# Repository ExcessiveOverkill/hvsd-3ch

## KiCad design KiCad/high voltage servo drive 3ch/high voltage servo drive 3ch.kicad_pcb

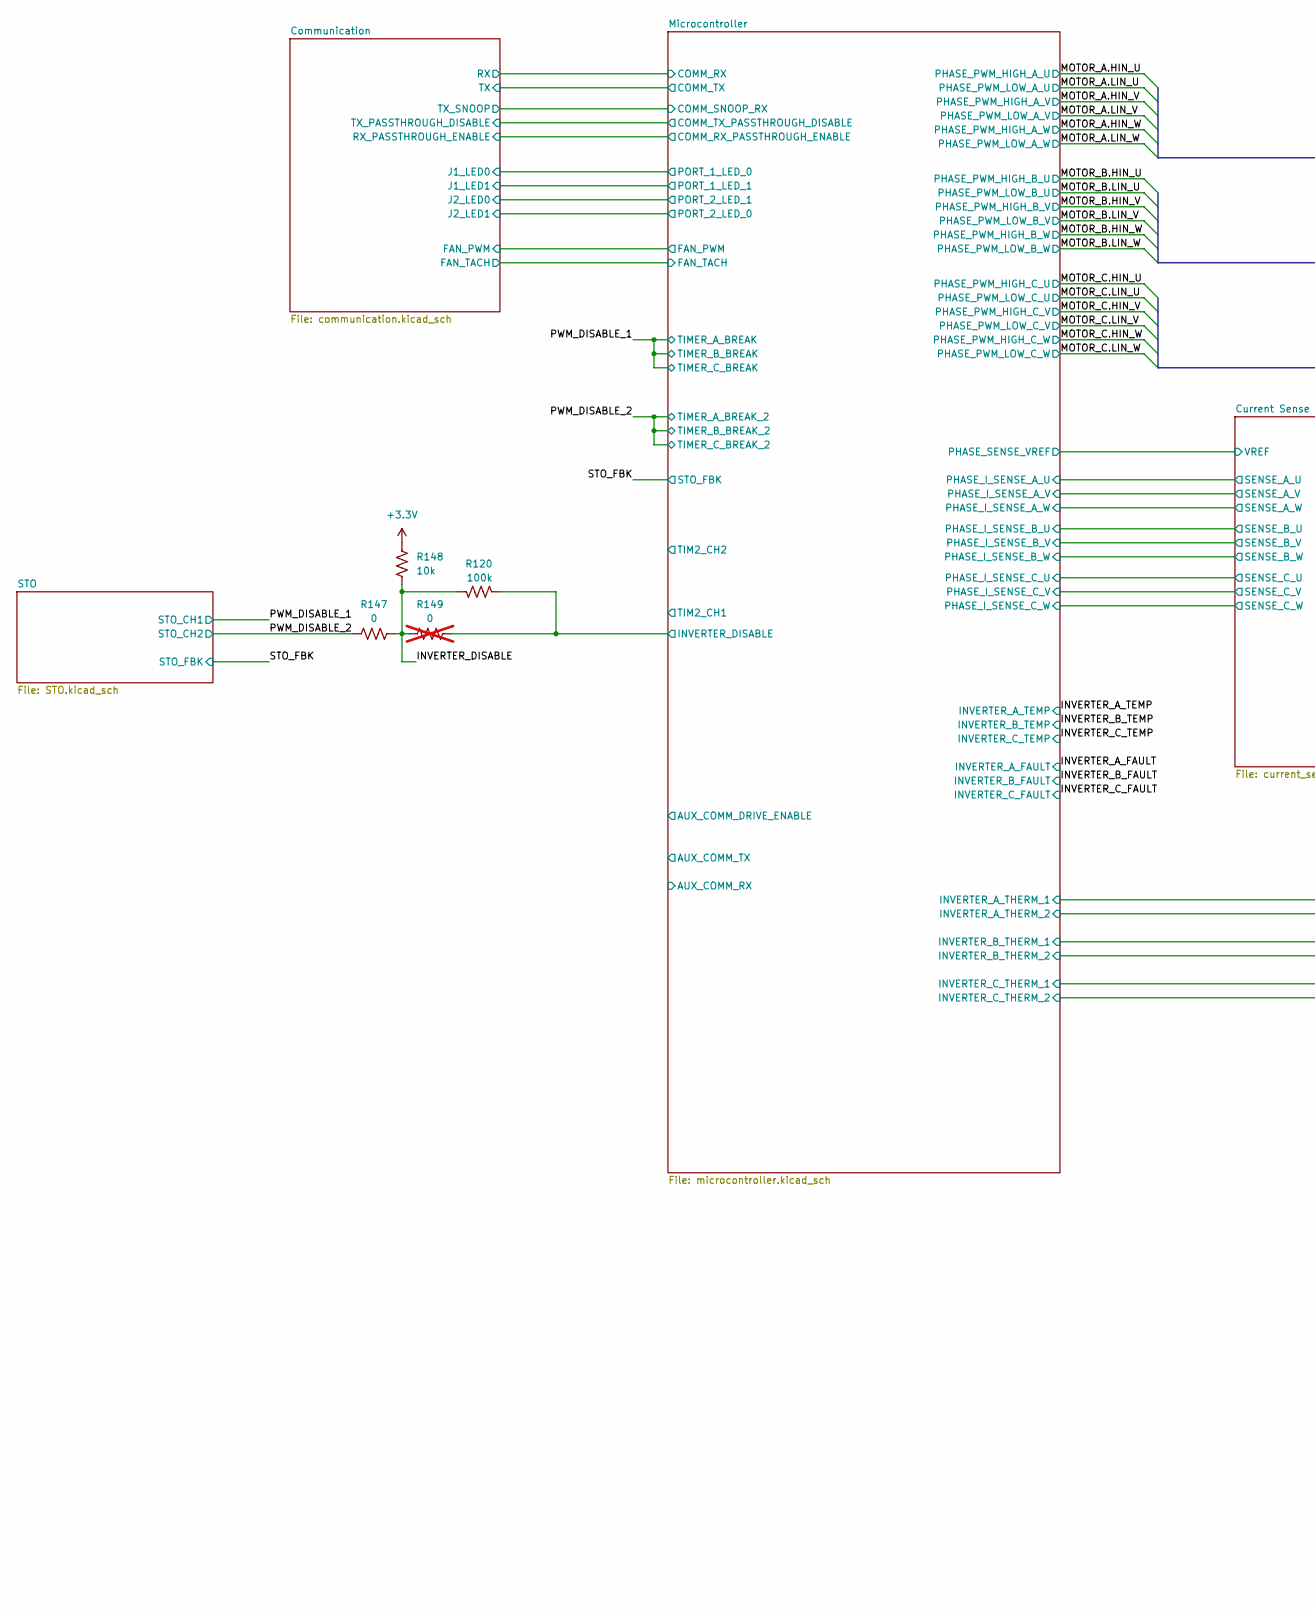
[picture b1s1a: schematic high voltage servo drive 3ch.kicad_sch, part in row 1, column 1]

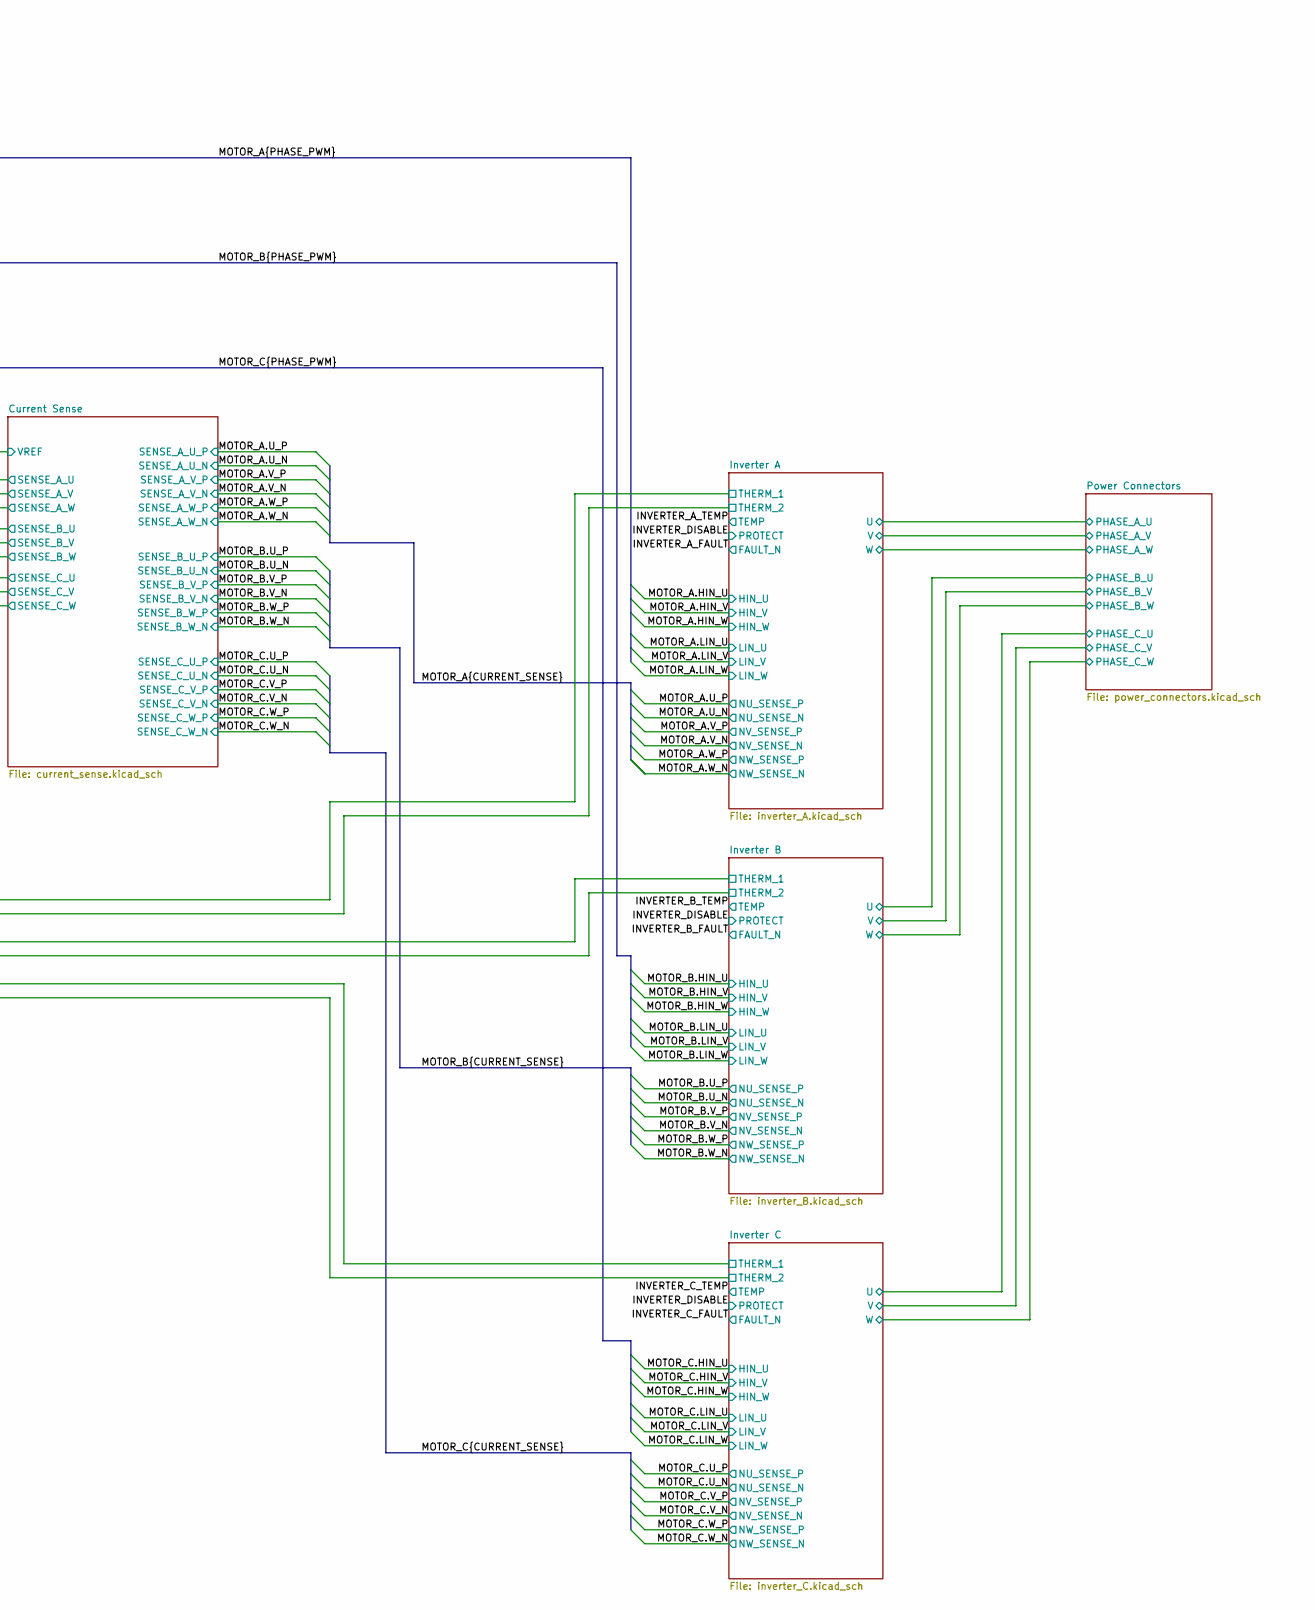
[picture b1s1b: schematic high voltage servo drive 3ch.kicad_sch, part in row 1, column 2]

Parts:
R120: 100k; R_0402_1005Metric; Part number RC0402FR-07100KL; LCSC# C60491
R147: 0; R_0402_1005Metric; Part number RC0402FR-070RL; LCSC# C106231
R148: 10k; R_0402_1005Metric; Part number RC0402FR-0710KL; LCSC# C60490
R149: 0; R_0402_1005Metric; Part number RC0402FR-070RL; LCSC# C106231; not fitted

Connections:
+3.3V: R148.2; also elsewhere on the board
/INVERTER_DISABLE: R120.2, R147.2, R148.1, R149.1; also elsewhere on the board
/Microcontroller/INVERTER_DISABLE: R120.1, R149.2; also elsewhere on the board
/PWM_DISABLE_2: R147.1; also elsewhere on the board

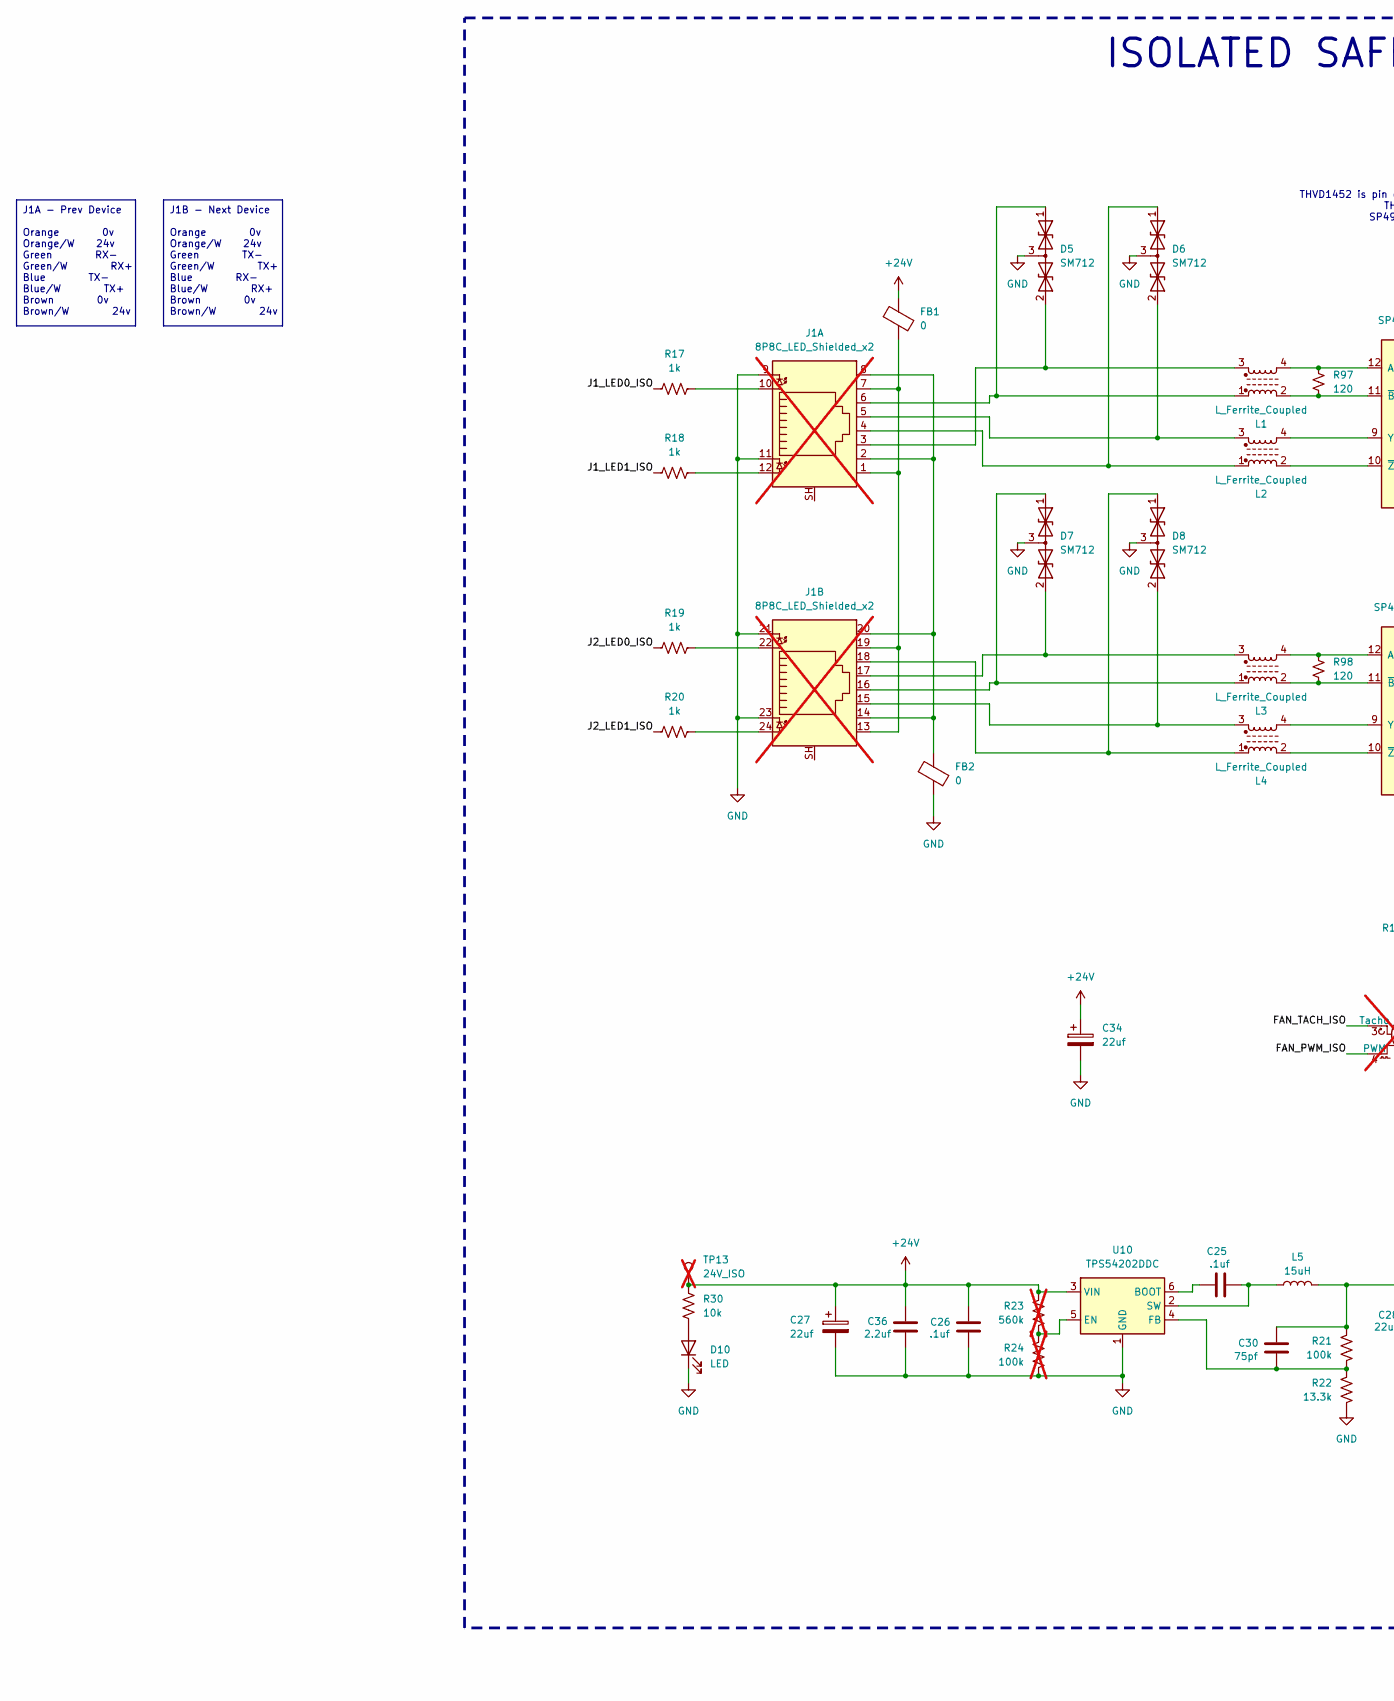
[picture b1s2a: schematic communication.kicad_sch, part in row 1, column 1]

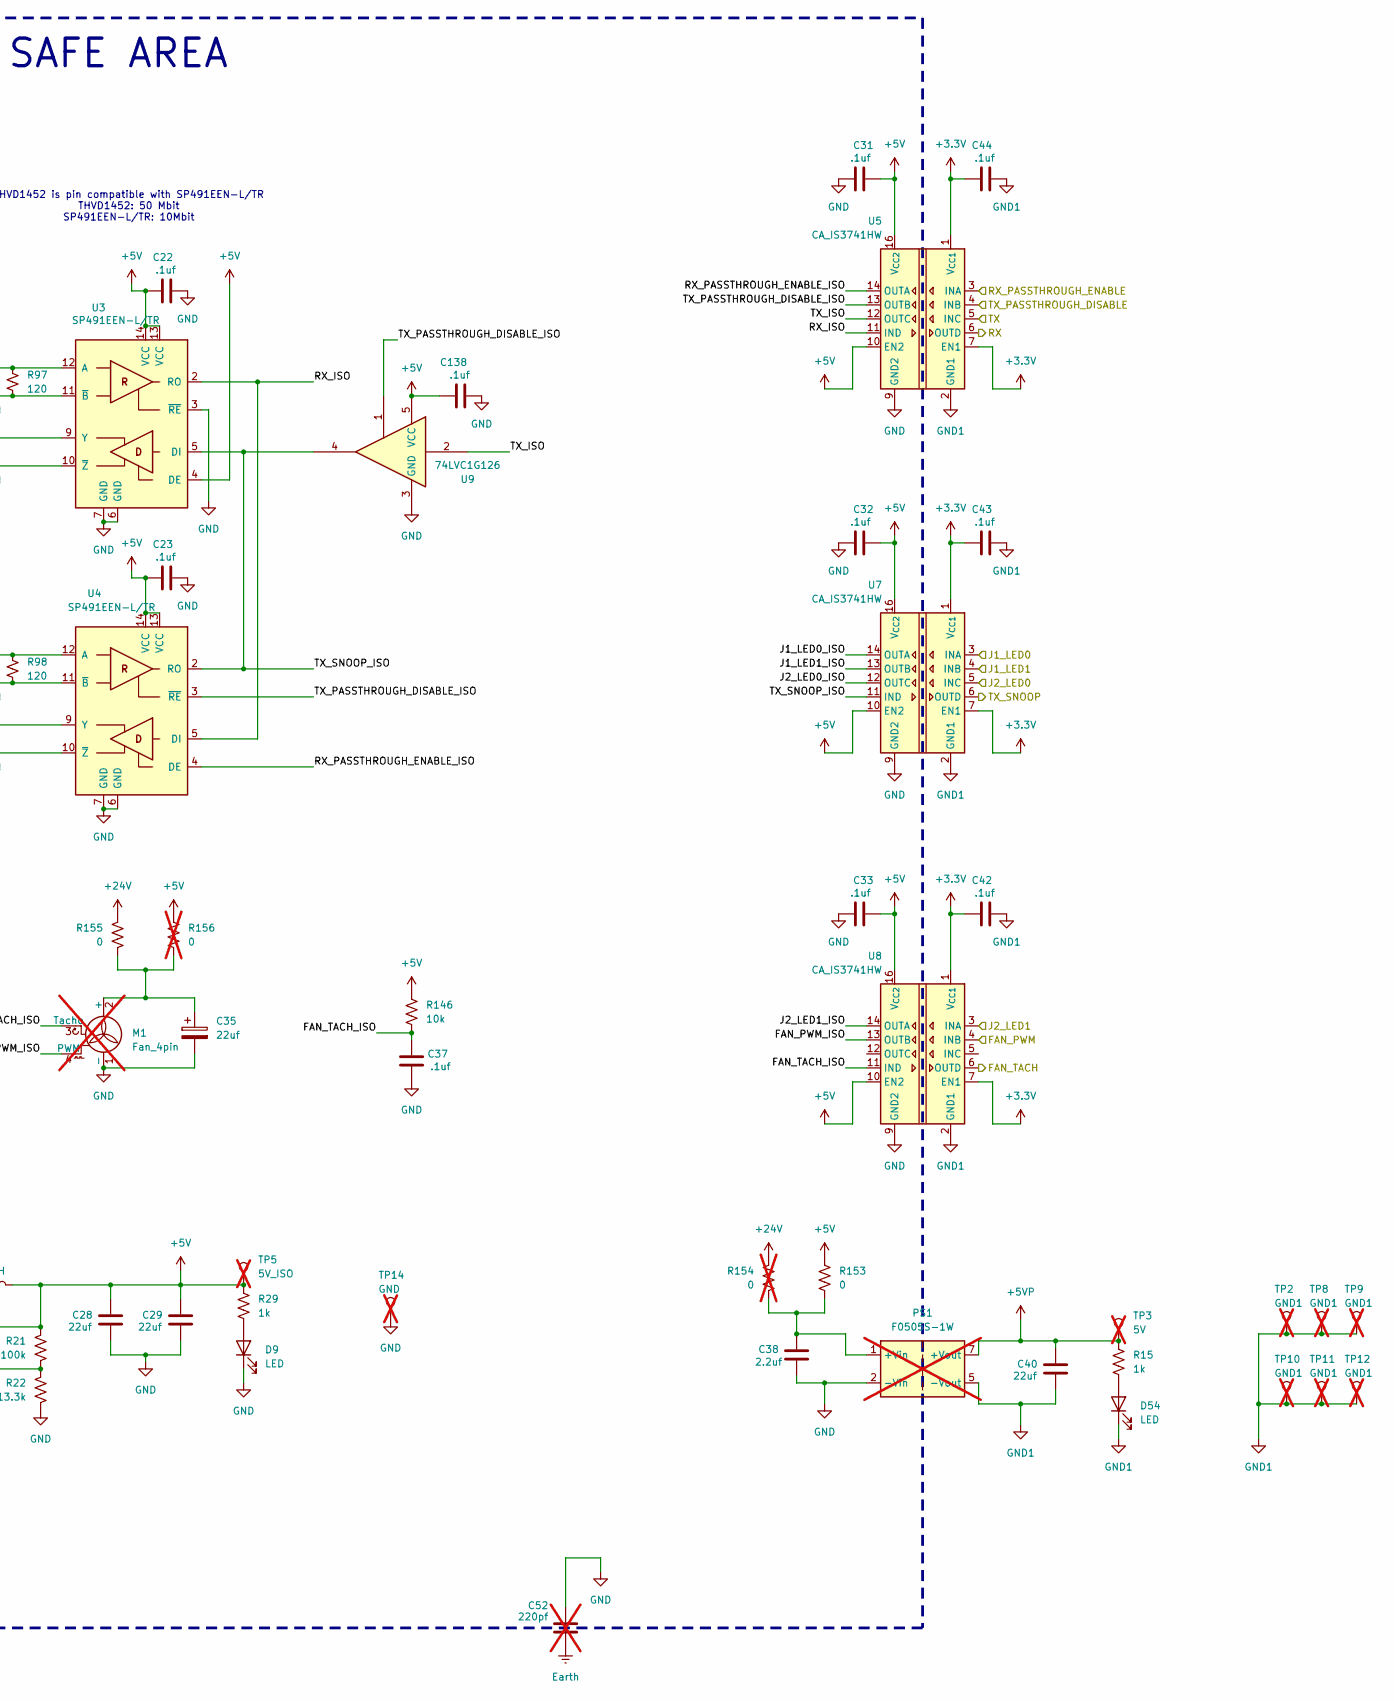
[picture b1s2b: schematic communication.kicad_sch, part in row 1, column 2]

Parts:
C22, C23, C25, C26, C31, C32, C33, C37, C42, C43, C44, C138: .1uf; C_0402_1005Metric; Part number CC0402KRX5R9BB104; LCSC# C105882
C27, C34, C35: 22uf; CP_Elec_6.3x5.9; Part number 189RV0014; LCSC# C7471876
C28, C29, C40: 22uf; C_1206_3216Metric; Part number CL31A226KAHNNNE; LCSC# C12891
C30: 75pf; C_0402_1005Metric; Part number CC0402JRNPO9BN750; LCSC# C107010
C36, C38: 2.2uf; C_1206_3216Metric; Part number CL31B225KBHNNNE; LCSC# C50254
C52: 220pf; C_Disc_D9.0mm_W5.0mm_P10.00mm; not fitted
D5, D6, D7, D8: SM712; SOT-23; Part number CDSOT23-SM712-ES; LCSC# C5199207
D9, D10, D54: LED; LED_0603_1608Metric; Part number XL-1608UGC-04; LCSC# C965804
FB1, FB2: 0; L_0805_2012Metric; Part number FRC0805P000 TS; LCSC# C2907288
J1: 8P8C_LED_Shielded_x2; RJ45_XDRJ-1609-002; Part number XDRJ-1609-002; LCSC# C7498193; not fitted
L1, L2, L3, L4: L_Ferrite_Coupled; SMD-4P,2x1.2mm; Part number CND-WCM0805M801-2; LCSC# C3020807
L5: 15uH; CY54_INDUCTOR; Part number CY54-15UH; LCSC# C2929432
M1: Fan_4pin; PinHeader_1x04_P2.54mm_Vertical; not fitted
PS1: F0505S-1W; Converter_DCDC_FXXS-1W; Part number F0505S-1WR3; LCSC# C2992398; not fitted
R15, R17, R18, R19, R20, R29: 1k; R_0402_1005Metric; Part number RC0402FR-071KL; LCSC# C106235
R21: 100k; R_0402_1005Metric; Part number RC0402FR-07100KL; LCSC# C60491
R22: 13.3k; R_0402_1005Metric; Part number RC0402FR-0713K3L; LCSC# C274352
R23: 560k; R_0402_1005Metric; Part number RC0402FR-07560KL; LCSC# C137958; not fitted
R24: 100k; R_0402_1005Metric; Part number RC0402FR-07100KL; LCSC# C60491; not fitted
R30, R146: 10k; R_0402_1005Metric; Part number RC0402FR-0710KL; LCSC# C60490
R97, R98: 120; R_0402_1005Metric; Part number RC0402FR-07120RL; LCSC# C114758
R153, R155: 0; R_0402_1005Metric; Part number RC0402FR-070RL; LCSC# C106231
R154, R156: 0; R_0402_1005Metric; Part number RC0402FR-070RL; LCSC# C106231; not fitted
TP2, TP8, TP9, TP10, TP11, TP12: GND1; TestPoint_THTPad_D2.0mm_Drill1.0mm; not fitted
TP3: 5V; TestPoint_Pad_D2.0mm; not fitted
TP5: 5V_ISO; TestPoint_Pad_D2.0mm; not fitted
TP13: 24V_ISO; TestPoint_Pad_D2.0mm; not fitted
TP14: GND; TestPoint_THTPad_D2.0mm_Drill1.0mm; not fitted
U3, U4: SP491EEN-L/TR; SOIC-14_3.9x8.7mm_P1.27mm; Part number SP491EEN-L/TR; LCSC# C32476
U5, U7, U8: CA_IS3741HW; SOIC-16W_7.5x10.3mm_P1.27mm; Part number CA-IS3741HW; LCSC# C428890
U9: 74LVC1G126; SOT-353_SC-70-5; Part number 74LVC1G126CT05ARCQ; LCSC# C48391411
U10: TPS54202DDC; SOT-23-6; Part number TPS54202DDCR; LCSC# C191884

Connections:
+3.3V: C42.1, C43.1, C44.1, U5.1 (V_{CC1}), U5.7 (EN1), U7.1 (V_{CC1}), U7.7 (EN1), U8.1 (V_{CC1}), U8.7 (EN1); also elsewhere on the board
+5V: C22.1, C23.1, C28.2, C29.2, C30.2, C31.1, C32.1, C33.1, C138.1, L5.2, R21.2, R29.2, R146.2, R153.2, R156.2, TP5.1, U3.4 (DE), U3.13 (VCC), U3.14 (VCC), U4.13 (VCC), U4.14 (VCC), U5.10 (EN2), U5.16 (V_{CC2}), U7.10 (EN2), U7.16 (V_{CC2}), U8.10 (EN2), U8.16 (V_{CC2}), U9.5 (VCC)
+5VP: C40.2, PS1.7 (+Vout), R15.2, TP3.1; also elsewhere on the board
+24V: C26.2, C27.1, C34.1, C36.2, FB1.1, R23.2, R30.2, R154.2, R155.2, TP13.1, U10.3 (VIN)
/Communication/FAN_PWM: U8.4 (INB); also elsewhere on the board
/Communication/FAN_PWM_ISO: M1.4 (PWM), U8.13 (OUTB)
/Communication/FAN_TACH: U8.6 (OUTD); also elsewhere on the board
/Communication/FAN_TACH_ISO: C37.1, M1.3 (Tacho), R146.1, U8.11 (IND)
/Communication/J1_LED0: U7.3 (INA); also elsewhere on the board
/Communication/J1_LED0_ISO: R17.1, U7.14 (OUTA)
/Communication/J1_LED1: U7.4 (INB); also elsewhere on the board
/Communication/J1_LED1_ISO: R18.1, U7.13 (OUTB)
/Communication/J2_LED0: U7.5 (INC); also elsewhere on the board
/Communication/J2_LED0_ISO: R19.1, U7.12 (OUTC)
/Communication/J2_LED1: U8.3 (INA); also elsewhere on the board
/Communication/J2_LED1_ISO: R20.1, U8.14 (OUTA)
/Communication/RX_ISO: U3.2 (RO), U4.5 (DI), U5.11 (IND)
/Communication/RX_PASSTHROUGH_ENABLE: U5.3 (INA); also elsewhere on the board
/Communication/RX_PASSTHROUGH_ENABLE_ISO: U4.4 (DE), U5.14 (OUTA)
/Communication/TX: U5.5 (INC); also elsewhere on the board
/Communication/TX_ISO: U5.12 (OUTC), U9.2
/Communication/TX_PASSTHROUGH_DISABLE: U5.4 (INB); also elsewhere on the board
/Communication/TX_PASSTHROUGH_DISABLE_ISO: U4.3 (~RE), U5.13 (OUTB), U9.1
/Communication/TX_SNOOP: U7.6 (OUTD); also elsewhere on the board
/Communication/TX_SNOOP_ISO: U3.5 (DI), U4.2 (RO), U7.11 (IND), U9.4
/Microcontroller/COMM_RX: U5.6 (OUTD); also elsewhere on the board
GND: C22.2, C23.2, C26.1, C27.2, C28.1, C29.1, C31.2, C32.2, C33.2, C34.2, C35.2, C36.1, C37.2, C38.1, C52.2, C138.2, D5.3 (common), D6.3 (common), D7.3 (common), D8.3 (common), D9.1 (K), D10.1 (K), FB2.2, J1.9, J1.11, J1.21, J1.23, M1.1 (-), PS1.2 (-Vin), R22.1, R24.1, TP14.1, U3.3 (~RE), U3.6 (GND), U3.7 (GND), U4.6 (GND), U4.7 (GND), U5.9 (GND2), U5.15 (GND2), U7.9 (GND2), U7.15 (GND2), U8.9 (GND2), U8.15 (GND2), U9.3 (GND), U10.1 (GND)
unnamed: D5.1 (A1), J1.6, L1.1
unnamed: D5.2 (A2), J1.3, L1.3
unnamed: D6.1 (A1), J1.4, L2.1
unnamed: D6.2 (A2), J1.5, L2.3
unnamed: D7.1 (A1), J1.16, L3.1
unnamed: D7.2 (A2), J1.17, L3.3
unnamed: D8.1 (A1), J1.18, L4.1
unnamed: D8.2 (A2), J1.15, L4.3
unnamed: D9.2 (A), R29.1
unnamed: D10.2 (A), R30.1
unnamed: D54.2 (A), R15.1
unnamed: FB1.2, J1.1, J1.7, J1.13, J1.19
unnamed: FB2.1, J1.2, J1.8, J1.14, J1.20
unnamed: J1.10, R17.2
unnamed: J1.12, R18.2
unnamed: J1.22, R19.2
unnamed: J1.24, R20.2
unnamed: C35.1, M1.2 (+), R155.1, R156.1
unnamed: C38.2, PS1.1 (+Vin), R153.1, R154.1
unnamed: L1.4, R97.1, U3.12 (A)
unnamed: L2.4, U3.9 (Y)
unnamed: L1.2, R97.2, U3.11 (~B)
unnamed: L2.2, U3.10 (~Z)
unnamed: L3.4, R98.1, U4.12 (A)
unnamed: L4.4, U4.9 (Y)
unnamed: L3.2, R98.2, U4.11 (~B)
unnamed: L4.2, U4.10 (~Z)
unnamed: C25.1, U10.6 (BOOT)
unnamed: R23.1, R24.2, U10.5 (EN)
unnamed: C30.1, R21.1, R22.2, U10.4 (FB)
unnamed: C25.2, L5.1, U10.2 (SW)

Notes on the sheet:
J1B - Next Device Orange 0v Orange/W 24v Green TX- Green/W TX+ Blue RX- Blue/W RX+ Brown 0v Brown/W 24v
J1A - Prev Device Orange 0v Orange/W 24v Green RX- Green/W RX+ Blue TX- Blue/W TX+ Brown 0v Brown/W 24v
THVD1452 is pin compatible with SP491EEN-L/TR THVD1452: 50 Mbit SP491EEN-L/TR: 10Mbit
ISOLATED SAFE AREA

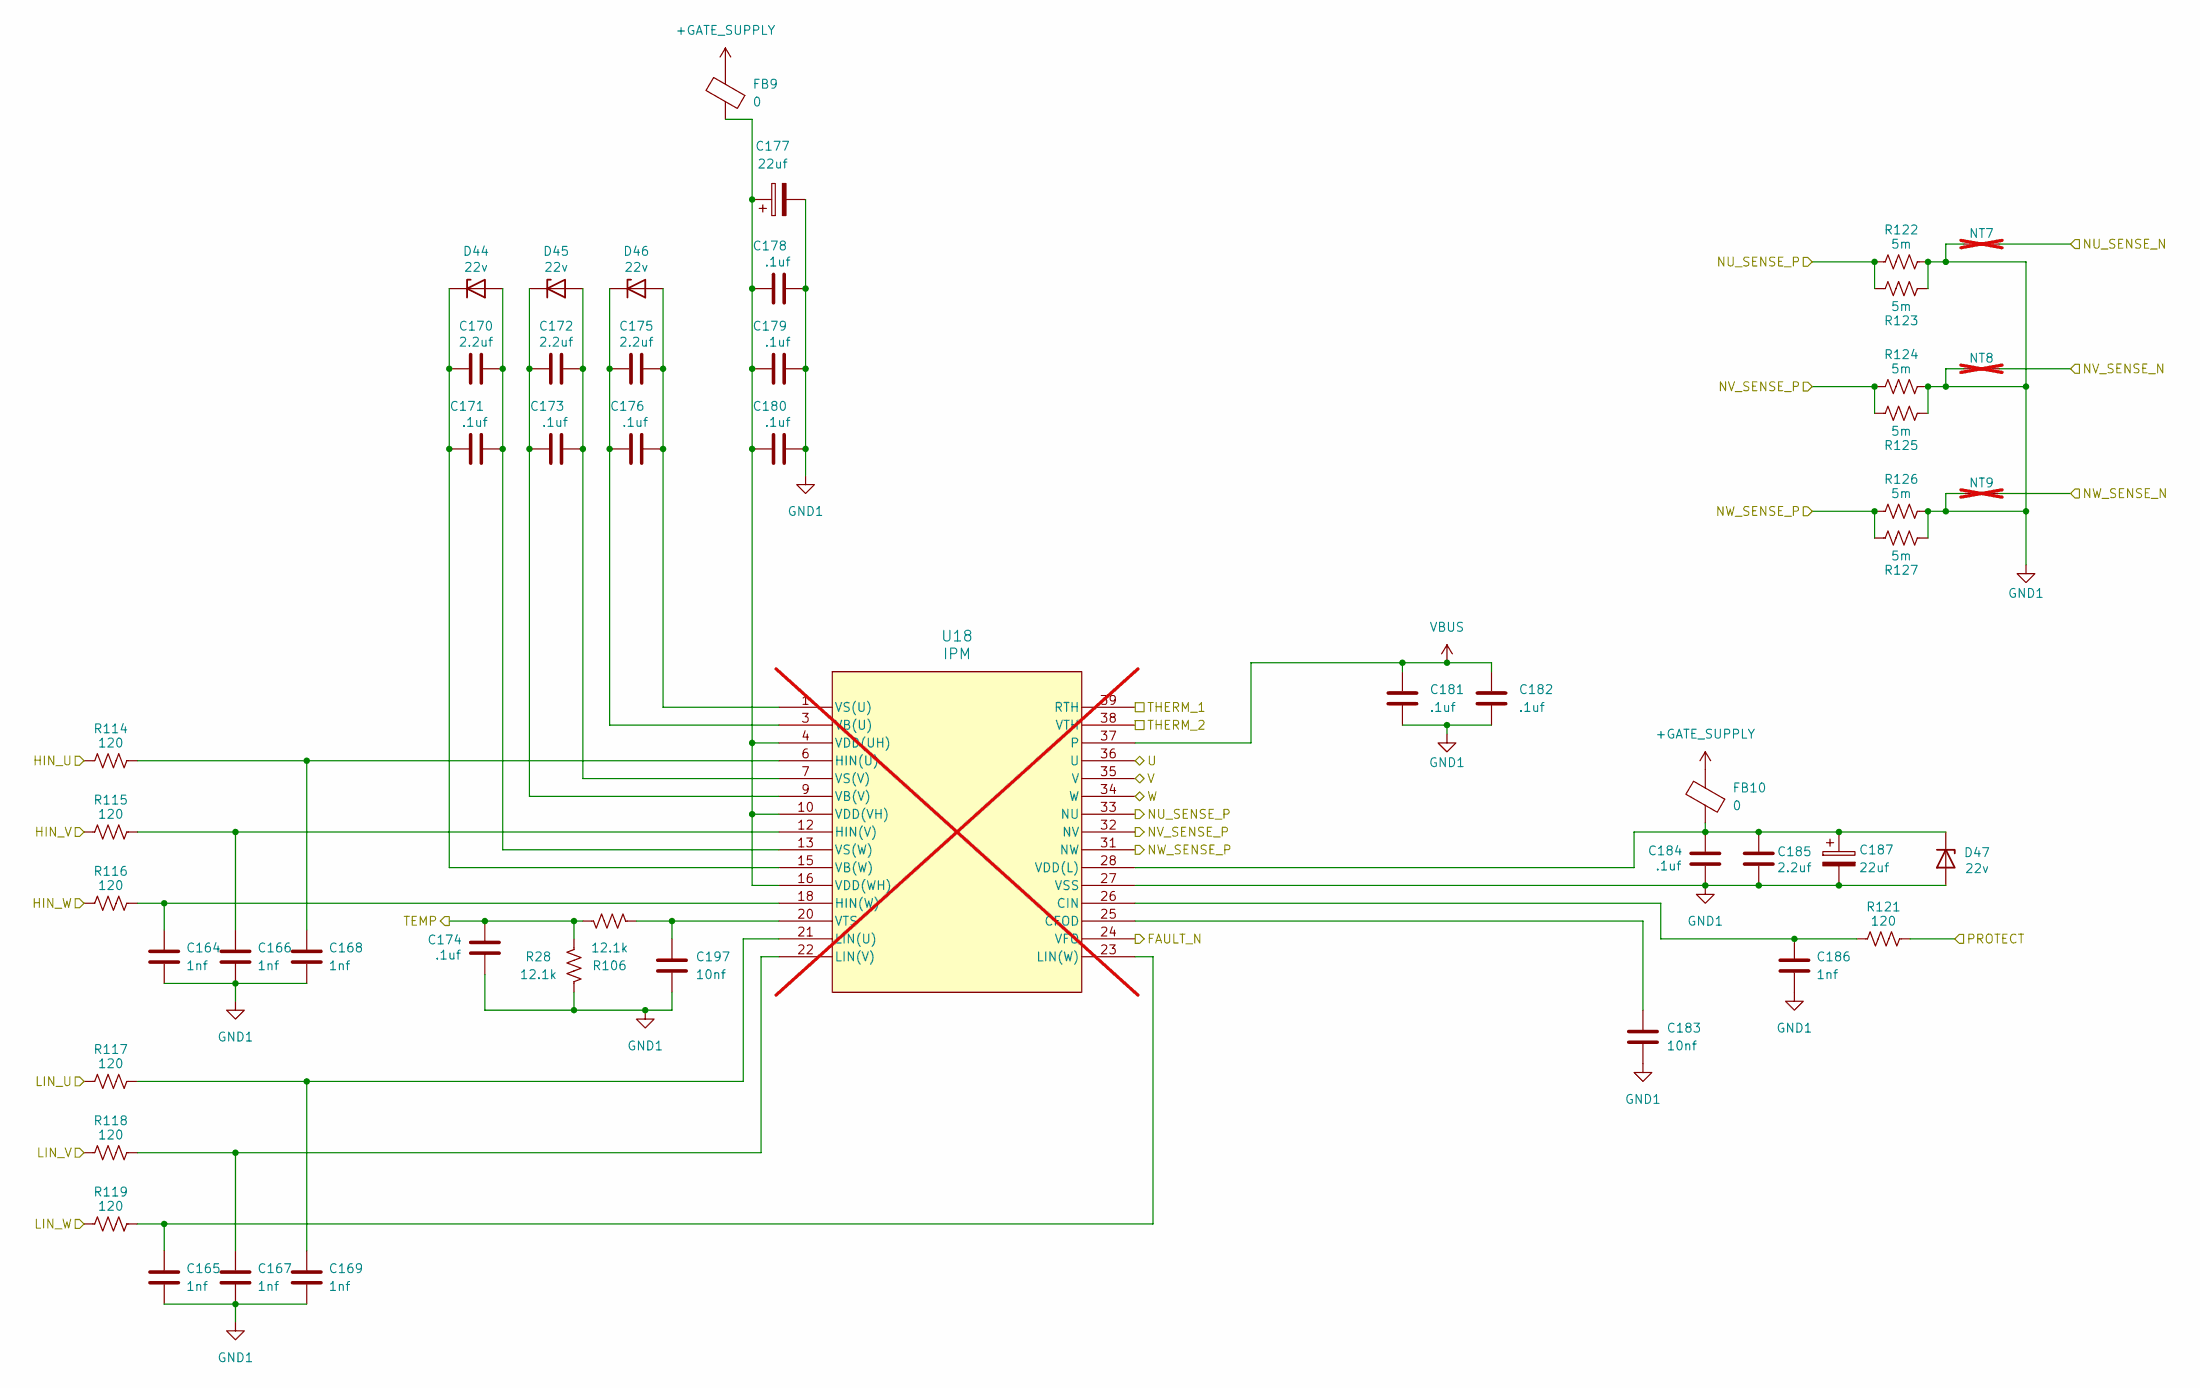
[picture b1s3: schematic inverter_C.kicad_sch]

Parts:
C164, C165, C166, C167, C168, C169, C186: 1nf; C_0402_1005Metric; Part number CC0402KRX7R9BB102; LCSC# C106205
C170, C172, C175, C185: 2.2uf; C_1206_3216Metric; Part number CL31B225KBHNNNE; LCSC# C50254
C171, C173, C174, C176, C178, C179, C180, C184: .1uf; C_0402_1005Metric; Part number CC0402KRX5R9BB104; LCSC# C105882
C177, C187: 22uf; CP_Elec_6.3x5.9; Part number 189RV0014; LCSC# C7471876
C181, C182: .1uf; C_1812_4532Metric; Part number NV1812B104K102CEMN; LCSC# C780707
C183, C197: 10nf; C_0402_1005Metric; Part number CC0402KRX7R9BB103; LCSC# C60133
D44, D45, D46, D47: 22v; D_SMA; Part number SMA2Z22A; LCSC# C7440711
FB9, FB10: 0; L_0805_2012Metric; Part number FRC0805P000 TS; LCSC# C2907288
NT7, NT8, NT9: NetTie_2; NetTie-2_SMD_Pad0.2mm; not fitted
R28, R106: 12.1k; R_0402_1005Metric; Part number RC0402FR-0712K1L; LCSC# C132157
R114, R115, R116, R117, R118, R119, R121: 120; R_0402_1005Metric; Part number RC0402FR-07120RL; LCSC# C114758
R122, R123, R124, R125, R126, R127: 5m; R_1206_3216Metric; Part number FRM121WFR005TM; LCSC# C7419996
U18: IPM; DIP39_54.5X31.0_MODGC_OSI; not fitted

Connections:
+GATE_SUPPLY: FB9.2, FB10.2; also elsewhere on the board
/INVERTER_C_FAULT: U18.24 (VFO); also elsewhere on the board
/INVERTER_C_TEMP: C174.2, R28.1, R106.1; also elsewhere on the board
/INVERTER_DISABLE: R121.2; also elsewhere on the board
/Inverter C/THERM_1: U18.39 (RTH); also elsewhere on the board
/Inverter C/U: U18.36 (U); also elsewhere on the board
/Inverter C/V: U18.35 (V); also elsewhere on the board
/Inverter C/W: U18.34 (W); also elsewhere on the board
/MOTOR_C.HIN_U: R114.1; also elsewhere on the board
/MOTOR_C.HIN_V: R115.1; also elsewhere on the board
/MOTOR_C.HIN_W: R116.1; also elsewhere on the board
/MOTOR_C.LIN_U: R117.1; also elsewhere on the board
/MOTOR_C.LIN_V: R118.1; also elsewhere on the board
/MOTOR_C.LIN_W: R119.1; also elsewhere on the board
/MOTOR_C.U_N: NT7.2; also elsewhere on the board
/MOTOR_C.U_P: R122.1, R123.2, U18.33 (NU); also elsewhere on the board
/MOTOR_C.V_N: NT8.2; also elsewhere on the board
/MOTOR_C.V_P: R124.1, R125.2, U18.32 (NV); also elsewhere on the board
/MOTOR_C.W_N: NT9.2; also elsewhere on the board
/MOTOR_C.W_P: R126.1, R127.2, U18.31 (NW); also elsewhere on the board
/Microcontroller/INVERTER_C_THERM: U18.38 (VTH); also elsewhere on the board
unnamed: C170.2, C171.2, D44.2 (A), U18.13 (VS(W))
unnamed: C170.1, C171.1, D44.1 (K), U18.15 (VB(W))
unnamed: C172.2, C173.2, D45.2 (A), U18.7 (VS(V))
unnamed: C172.1, C173.1, D45.1 (K), U18.9 (VB(V))
unnamed: C175.2, C176.2, D46.2 (A), U18.1 (VS(U))
unnamed: C175.1, C176.1, D46.1 (K), U18.3 (VB(U))
unnamed: C184.2, C185.1, C187.1, D47.1 (K), FB10.1, U18.28 (VDD(L))
unnamed: C183.1, U18.25 (CFOD)
unnamed: C186.1, R121.1, U18.26 (CIN)
unnamed: C168.1, R114.2, U18.6 (HIN(U))
unnamed: C166.1, R115.2, U18.12 (HIN(V))
unnamed: C164.1, R116.2, U18.18 (HIN(W))
unnamed: C169.1, R117.2, U18.21 (LIN(U))
unnamed: C167.1, R118.2, U18.22 (LIN(V))
unnamed: C165.1, R119.2, U18.23 (LIN(W))
unnamed: C177.1, C178.1, C179.1, C180.1, FB9.1, U18.4 (VDD(UH)), U18.10 (VDD(VH)), U18.16 (VDD(WH))
unnamed: C197.1, R106.2, U18.20 (VTS)
VBUS: C181.1, C182.1, U18.37; also elsewhere on the board

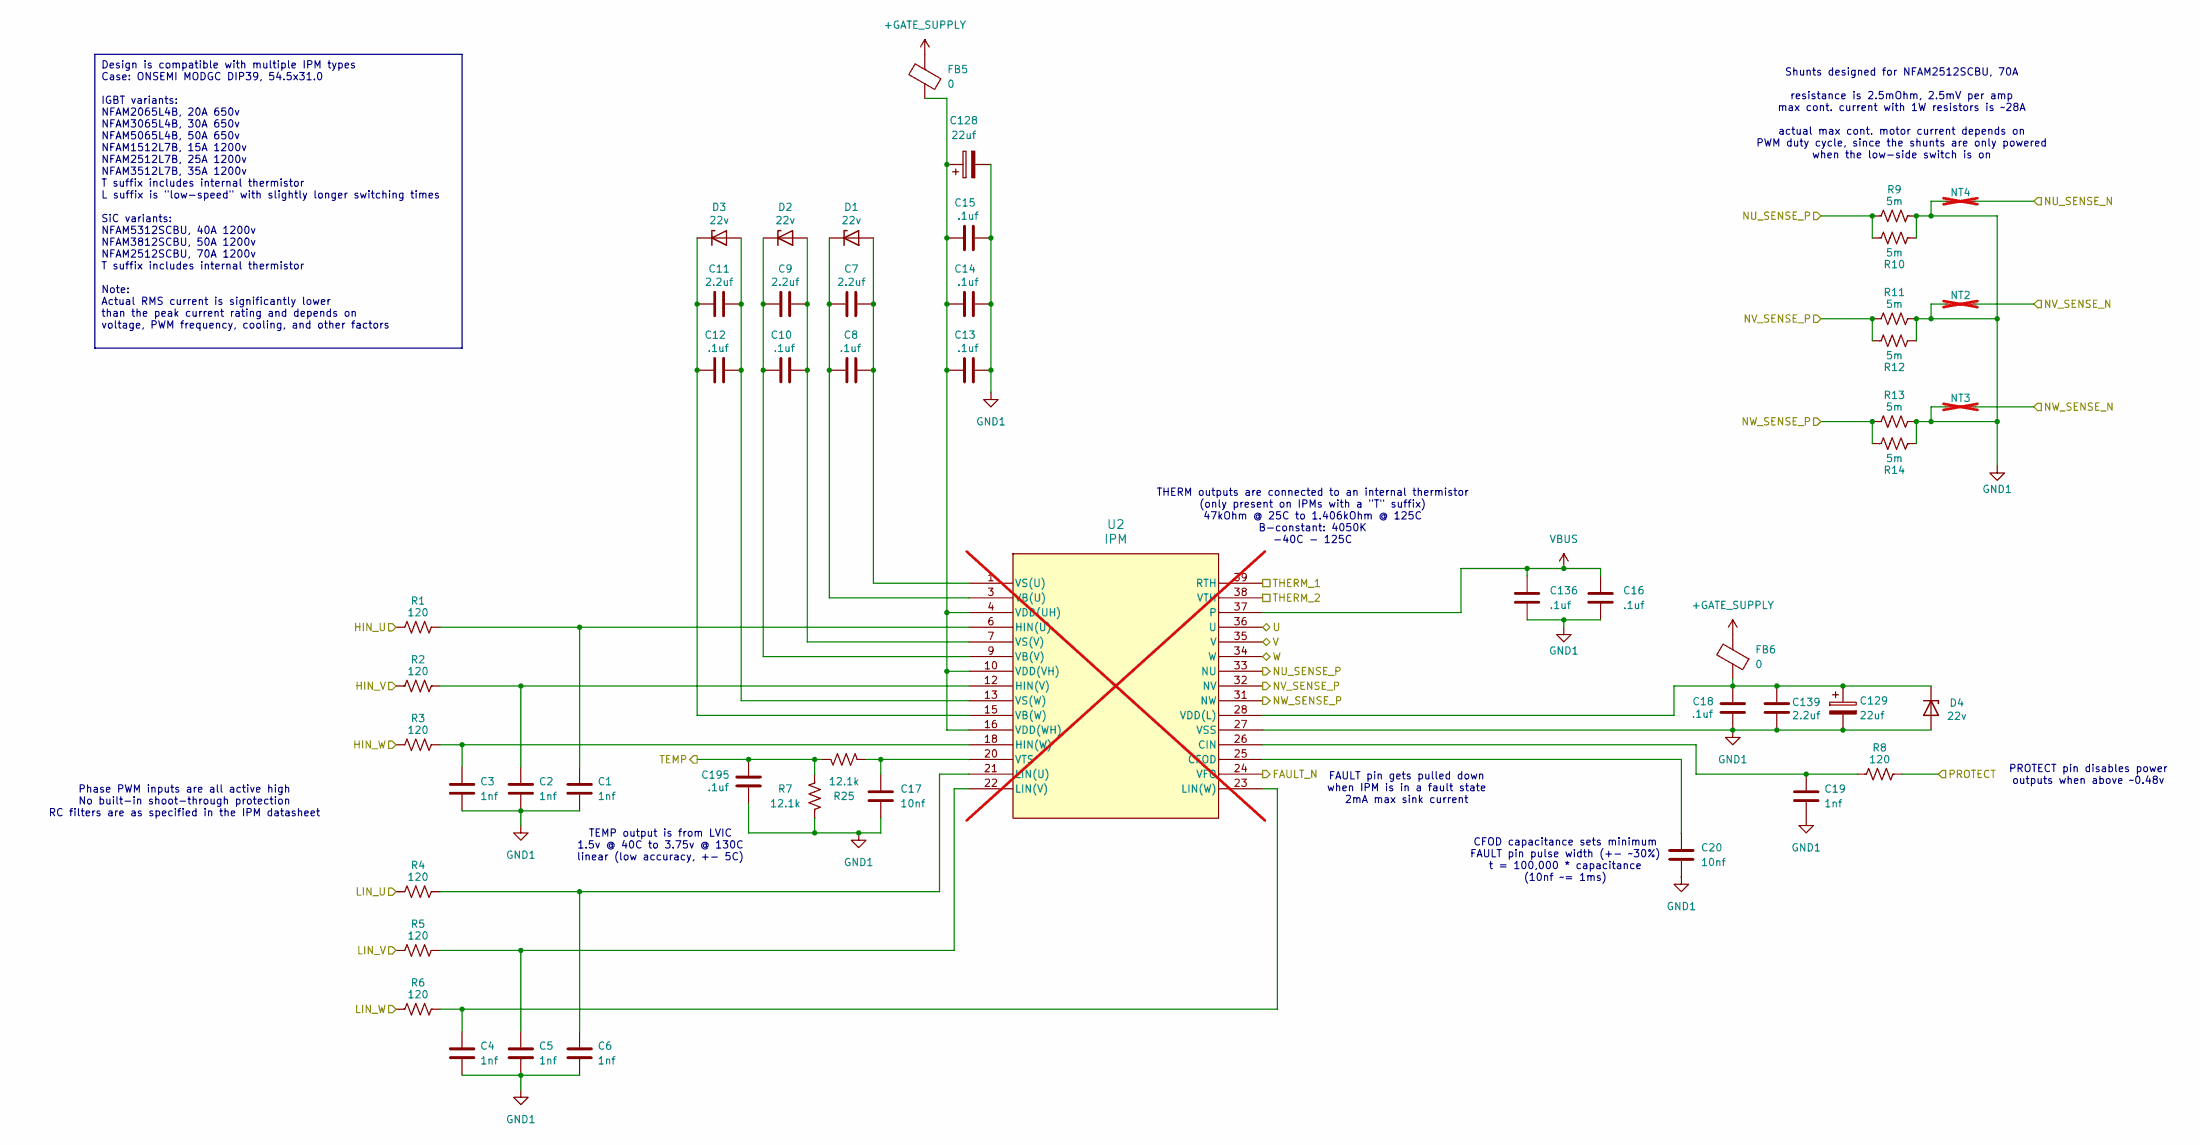
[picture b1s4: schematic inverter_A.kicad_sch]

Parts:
C1, C2, C3, C4, C5, C6, C19: 1nf; C_0402_1005Metric; Part number CC0402KRX7R9BB102; LCSC# C106205
C7, C9, C11, C139: 2.2uf; C_1206_3216Metric; Part number CL31B225KBHNNNE; LCSC# C50254
C8, C10, C12, C13, C14, C15, C18, C195: .1uf; C_0402_1005Metric; Part number CC0402KRX5R9BB104; LCSC# C105882
C16, C136: .1uf; C_1812_4532Metric; Part number NV1812B104K102CEMN; LCSC# C780707
C17, C20: 10nf; C_0402_1005Metric; Part number CC0402KRX7R9BB103; LCSC# C60133
C128, C129: 22uf; CP_Elec_6.3x5.9; Part number 189RV0014; LCSC# C7471876
D1, D2, D3, D4: 22v; D_SMA; Part number SMA2Z22A; LCSC# C7440711
FB5, FB6: 0; L_0805_2012Metric; Part number FRC0805P000 TS; LCSC# C2907288
NT2, NT3, NT4: NetTie_2; NetTie-2_SMD_Pad0.2mm; not fitted
R1, R2, R3, R4, R5, R6, R8: 120; R_0402_1005Metric; Part number RC0402FR-07120RL; LCSC# C114758
R7, R25: 12.1k; R_0402_1005Metric; Part number RC0402FR-0712K1L; LCSC# C132157
R9, R10, R11, R12, R13, R14: 5m; R_1206_3216Metric; Part number FRM121WFR005TM; LCSC# C7419996
U2: IPM; DIP39_54.5X31.0_MODGC_OSI; not fitted

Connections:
+GATE_SUPPLY: FB5.2, FB6.2; also elsewhere on the board
/INVERTER_A_FAULT: U2.24 (VFO); also elsewhere on the board
/INVERTER_A_TEMP: C195.2, R7.1, R25.1; also elsewhere on the board
/INVERTER_DISABLE: R8.2; also elsewhere on the board
/Inverter A/THERM_1: U2.39 (RTH); also elsewhere on the board
/Inverter A/U: U2.36 (U); also elsewhere on the board
/Inverter A/V: U2.35 (V); also elsewhere on the board
/Inverter A/W: U2.34 (W); also elsewhere on the board
/MOTOR_A.HIN_U: R1.1; also elsewhere on the board
/MOTOR_A.HIN_V: R2.1; also elsewhere on the board
/MOTOR_A.HIN_W: R3.1; also elsewhere on the board
/MOTOR_A.LIN_U: R4.1; also elsewhere on the board
/MOTOR_A.LIN_V: R5.1; also elsewhere on the board
/MOTOR_A.LIN_W: R6.1; also elsewhere on the board
/MOTOR_A.U_N: NT4.2; also elsewhere on the board
/MOTOR_A.U_P: R9.1, R10.2, U2.33 (NU); also elsewhere on the board
/MOTOR_A.V_N: NT2.2; also elsewhere on the board
/MOTOR_A.V_P: R11.1, R12.2, U2.32 (NV); also elsewhere on the board
/MOTOR_A.W_N: NT3.2; also elsewhere on the board
/MOTOR_A.W_P: R13.1, R14.2, U2.31 (NW); also elsewhere on the board
/Microcontroller/INVERTER_A_THERM: U2.38 (VTH); also elsewhere on the board
unnamed: C7.2, C8.2, D1.2 (A), U2.1 (VS(U))
unnamed: C7.1, C8.1, D1.1 (K), U2.3 (VB(U))
unnamed: C9.2, C10.2, D2.2 (A), U2.7 (VS(V))
unnamed: C9.1, C10.1, D2.1 (K), U2.9 (VB(V))
unnamed: C11.2, C12.2, D3.2 (A), U2.13 (VS(W))
unnamed: C11.1, C12.1, D3.1 (K), U2.15 (VB(W))
unnamed: C18.2, C129.1, C139.1, D4.1 (K), FB6.1, U2.28 (VDD(L))
unnamed: C20.1, U2.25 (CFOD)
unnamed: C19.1, R8.1, U2.26 (CIN)
unnamed: C1.1, R1.2, U2.6 (HIN(U))
unnamed: C2.1, R2.2, U2.12 (HIN(V))
unnamed: C3.1, R3.2, U2.18 (HIN(W))
unnamed: C6.1, R4.2, U2.21 (LIN(U))
unnamed: C5.1, R5.2, U2.22 (LIN(V))
unnamed: C4.1, R6.2, U2.23 (LIN(W))
unnamed: C13.1, C14.1, C15.1, C128.1, FB5.1, U2.4 (VDD(UH)), U2.10 (VDD(VH)), U2.16 (VDD(WH))
unnamed: C17.1, R25.2, U2.20 (VTS)
VBUS: C16.1, C136.1, U2.37; also elsewhere on the board

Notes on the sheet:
Design is compatible with multiple IPM types Case: ONSEMI MODGC DIP39, 54.5x31.0 IGBT variants: NFAM2065L4B, 20A 650v NFAM3065L4B, 30A 650v NFAM5065L4B, 50A 650v NFAM1512L7B, 15A 1200v NFAM2512L7B, 25A 1200v NFAM3512L7B, 35A 1200v T suffix includes internal thermistor L suffix is "low-speed" with s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
TEMP output is from LVIC 1.5v @ 40C to 3.75v @ 130C linear (low accuracy, +- 5C)
CFOD capacitance sets minimum FAULT pin pulse width (+- ~30%) t = 100,000 * capacitance (10nf ~= 1ms)
Shunts designed for NFAM2512SCBU, 70A resistance is 2.5mOhm, 2.5mV per amp max cont. current with 1W resistors is ~28A actual max cont. motor current depends on PWM duty cycle, since the shunts are only powered when the low-side switch is on
THERM outputs are connected to an internal thermistor (only present on IPMs with a "T" suffix) 47kOhm @ 25C to 1.406kOhm @ 125C B-constant: 4050K -40C - 125C
FAULT pin gets pulled down when IPM is in a fault state 2mA max sink current
PROTECT pin disables power outputs when above ~0.48v
Phase PWM inputs are all active high No built-in shoot-through protection RC filters are as specified in the IPM datasheet
